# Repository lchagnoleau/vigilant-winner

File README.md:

# Vigilant-winner

Vigilant-winner is a emulator for USB Keyboard. It works on both Linux and Windows OS. MacOS is not testet yet.

You will find in this reposytory all both hardware and software file you need to make your own USB DUCK.

## Needs

To compile the software, you need **dfu-utils** installed on your system :

    sudo apt-get install dfu-util

## How to run

  Compile the flasher :

    cd flash
    make
    sudo make install

Generate your payload using this website : [Duck ToolKit](https://ducktoolkit.com/) and flash your USB key :

    winner-flash inject.bin

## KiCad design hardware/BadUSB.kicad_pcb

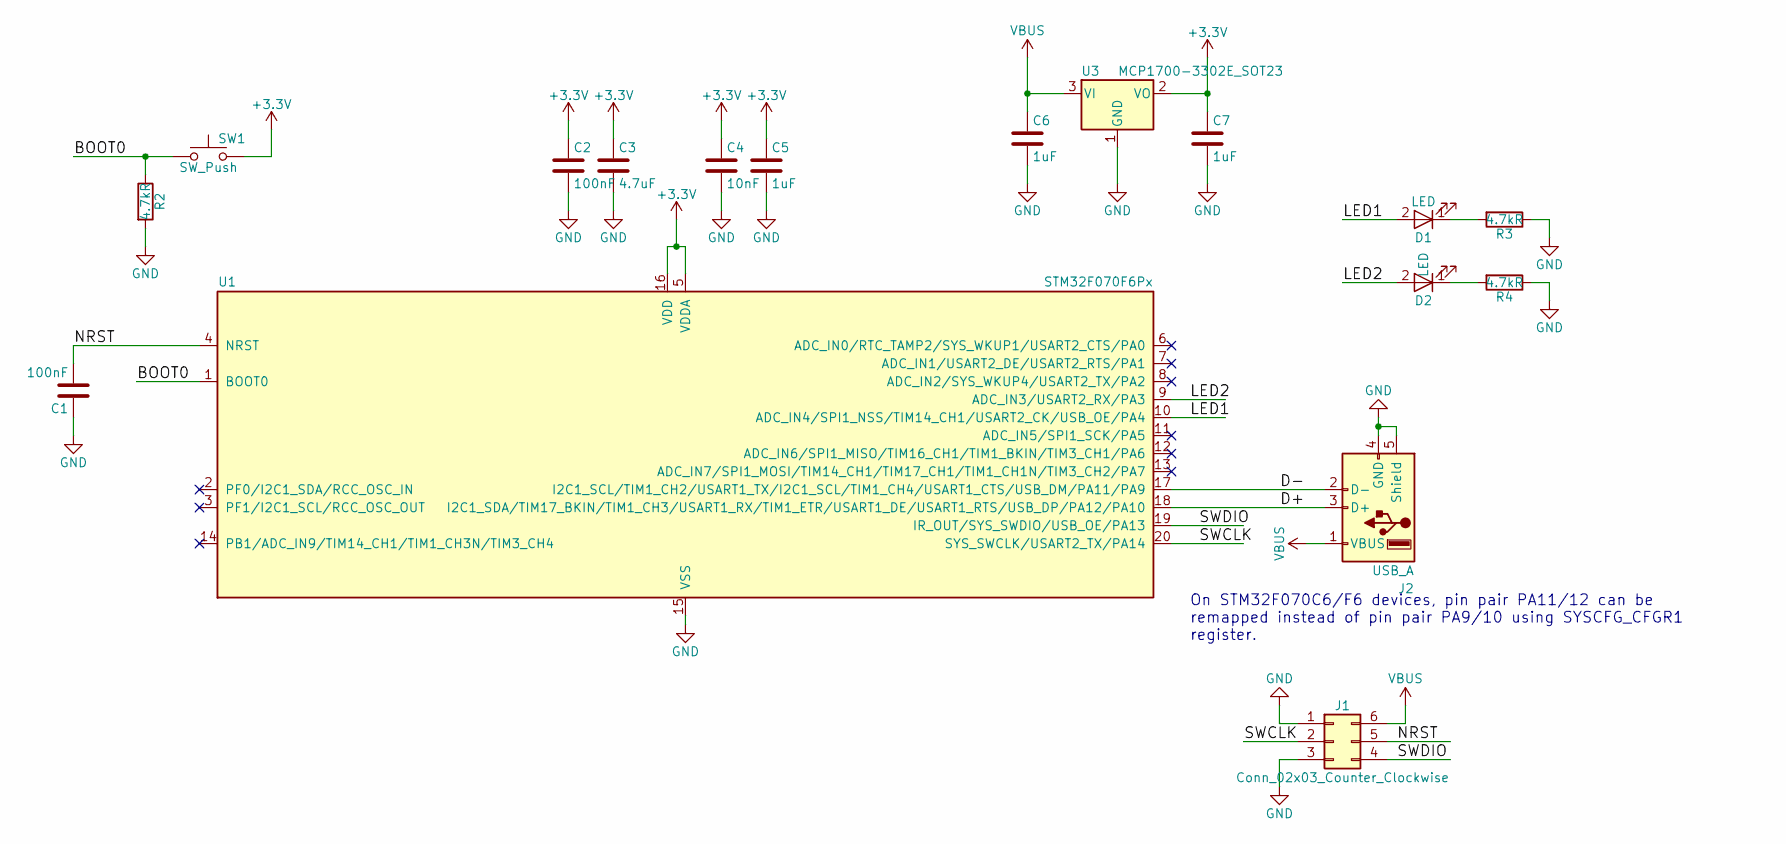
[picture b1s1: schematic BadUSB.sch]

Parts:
C1, C2: 100nF; c_0603
C3: 4.7uF; c_0603
C4: 10nF; c_0603
C5, C6, C7: 1uF; c_0603
D1, D2: LED; Led_0603
J1: Conn_02x03_Counter_Clockwise; pin_strip_2mm_3x2
J2: USB_A; USB_A_RECEPTACLE
R2, R3, R4: 4.7kR; r_0603
SW1: SW_Push; smd_push
U1: STM32F070F6Px; tssop-20
U3: MCP1700-3302E_SOT23; sot23

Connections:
+3V3: C2.1, C3.1, C4.1, C5.1, C7.1, SW1.2, U1.5 (VDDA), U1.16 (VDD), U3.2 (VO)
/BOOT0: R2.1, SW1.1, U1.1 (BOOT0)
/D+: J2.3 (D+), U1.18 (I2C1_SDA/TIM17_BKIN/TIM1_CH3/USART1_RX/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)
/D-: J2.2 (D-), U1.17 (I2C1_SCL/TIM1_CH2/USART1_TX/I2C1_SCL/TI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)
/LED1: D1.2 (A), U1.10 (ADC_IN4/SPI1_NSS/TIM14_CH1/USART2_CK/US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)
/LED2: D2.2 (A), U1.9 (ADC_IN3/USART2_RX/PA3)
/NRST: C1.2, J1.5, U1.4 (NRST)
/SWCLK: J1.2, U1.20 (SYS_SWCLK/USART2_TX/PA14)
/SWDIO: J1.4, U1.19 (IR_OUT/SYS_SWDIO/USB_OE/PA13)
GND: C1.1, C2.2, C3.2, C4.2, C5.2, C6.2, C7.2, J1.1, J1.3, J2.4 (GND), J2.5 (Shield), R2.2, R3.1, R4.1, U1.15 (VSS), U3.1 (GND)
unnamed: D1.1 (K), R3.2
unnamed: D2.1 (K), R4.2
VBUS: C6.1, J1.6, J2.1 (VBUS), U3.3 (VI)

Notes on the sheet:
On STM32F070C6/F6 devices, pin pair PA11/12 can be remapped instead of pin pair PA9/10 using SYSCFG_CFGR1 register.

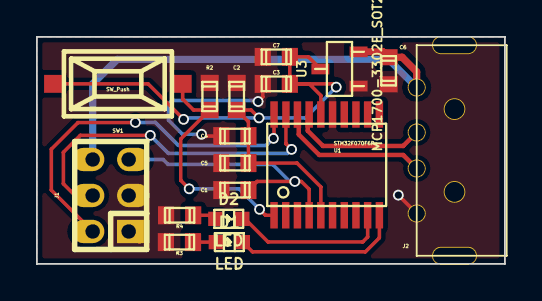
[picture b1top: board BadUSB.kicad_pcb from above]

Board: 2 copper layers, 26.0 x 12.6 mm, 17 parts (0 on the bottom side), 13 nets.

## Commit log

2018-04-12 USB works !
2018-04-12 works and add payload generator
2018-04-13 improvements
2018-08-24 change hardware
2018-08-24 add hardwer project
2018-08-24 remove file
2018-08-24 add master run script
2018-08-24 change readme
2018-08-24 bugfix
2018-08-28 add Makefile
2018-08-28 Add Section for duckraw
2018-08-28 Remove Release Folder
2018-08-28 Remove Files
2018-08-29 work in progress
2018-08-29 windows works
2018-09-06 Add patch bin
2018-09-06 add flash executable
2018-09-07 add install methode for make
2018-09-07 clean
2018-09-11 bug correction in USB Descriptor
